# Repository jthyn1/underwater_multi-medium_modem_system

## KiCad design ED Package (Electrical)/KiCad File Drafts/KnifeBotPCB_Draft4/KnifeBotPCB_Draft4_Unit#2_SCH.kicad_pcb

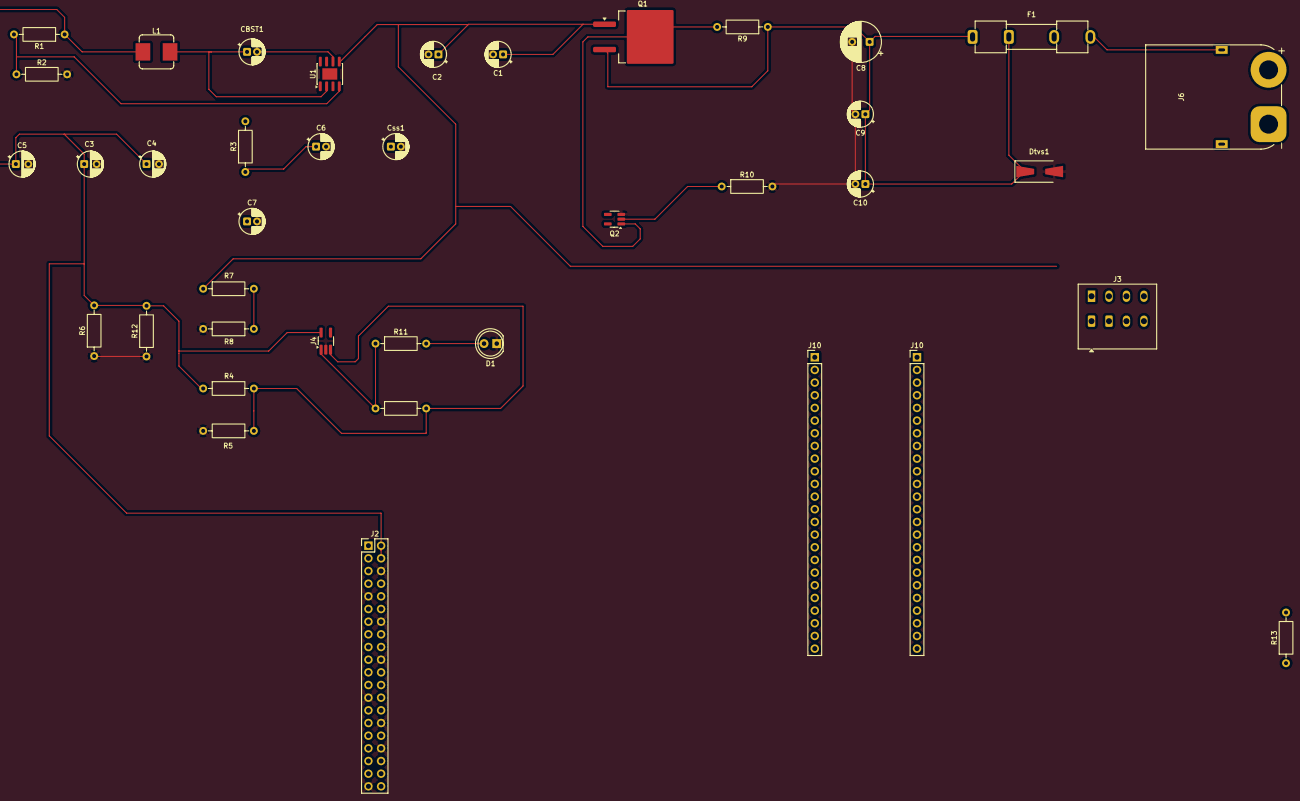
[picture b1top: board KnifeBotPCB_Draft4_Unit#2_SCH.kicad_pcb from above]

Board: 2 copper layers, 39 parts (0 on the bottom side), 17 nets.

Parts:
C1: 10uF; CP_Radial_D5.0mm_P2.00mm
C2, C10: 100nF; CP_Radial_D5.0mm_P2.00mm
C3, C4, C5: 22uF; CP_Radial_D5.0mm_P2.50mm
C6: 33pF; CP_Radial_D5.0mm_P2.00mm
C7: 2.7nF; CP_Radial_D5.0mm_P2.00mm
C8: 100uF; CP_Radial_D8.0mm_P3.50mm
C9: 1uF; CP_Radial_D5.0mm_P2.00mm
CBST1: 100nF; CP_Radial_D5.0mm_P2.00mm
Css1: 10nF; CP_Radial_D5.0mm_P2.00mm
D1: LED; LED_D5.0mm
Dtvs1: SMBJ18A; D_SMA-SMB_Universal_Handsoldering
F1: 5A; Fuseholder_Clip-5x20mm_Keystone_3512_Inline_P23.62x7.27mm_D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
J2: Raspberry_Pi_5; PinHeader_2x20_P2.54mm_Vertical
J3: WAGO 2604-3104PCB terminal block; TerminalBlock_WAGO_2601-3104_1x04_P3.50mm_Vertical
J4: TLV7031; TSOT-23-5_HandSoldering
J6: XT90PW-M; AMASS_XT90PW-M_1x02_P10.90mm_Horizontal
J10, J10#2: Teensy 4.1; PinHeader_1x24_P2.54mm_Vertical
L1: 3.6uH; L_Bourns_SRP7028A_7.3x6.6mm
Q1: F5305S PMOS; TO-263-2
Q2: BSS138 NMOS; SOT-23-5_HandSoldering
R1: 55k; R_Axial_DIN0207_L6.3mm_D2.5mm_P10.16mm_Horizontal
R2, R5, R8: 10k; R_Axial_DIN0207_L6.3mm_D2.5mm_P10.16mm_Horizontal
R3: 15.8k; R_Axial_DIN0207_L6.3mm_D2.5mm_P10.16mm_Horizontal
R4: 25.86k; R_Axial_DIN0207_L6.3mm_D2.5mm_P10.16mm_Horizontal
R6, R9, R10: 100k; R_Axial_DIN0207_L6.3mm_D2.5mm_P10.16mm_Horizontal
R7: 90k; R_Axial_DIN0207_L6.3mm_D2.5mm_P10.16mm_Horizontal
R11: 1k; R_Axial_DIN0207_L6.3mm_D2.5mm_P10.16mm_Horizontal
R12: 500k; R_Axial_DIN0207_L6.3mm_D2.5mm_P10.16mm_Horizontal
R13: 4.7k; R_Axial_DIN0207_L6.3mm_D2.5mm_P10.16mm_Horizontal
Rhys1: 470k; R_Axial_DIN0207_L6.3mm_D2.5mm_P10.16mm_Horizontal
U1: AP64501SP-13; SOIC-8-1EP_3.9x4.9mm_P1.27mm_EP2.29x3mm

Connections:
5V/5A: C3.1, C4.1, C5.1, J2.2 (5V), J2.4 (5V), J4.5 (VCC), L1.1, R1.1, R4.1, R6.2, R12.2
+VBATT: C1.1, C2.1, Q1.1 (D), R7.1, U1.3 (VIN), U1.5 (EN)
/1.45V Low Batt ref: J4.3 (In+), R4.2, R5.1, Rhys1.2
/Sensors&Teensy/Any Digital Pin: J10.23 (AIN1), R13.1
GND: C1.2, C2.2, C3.2, C4.2, C5.2, C6.2, C7.2, C8.2, C9.2, C10.2, Css1.2, D1.1 (K), Dtvs1.2 (A2), J2.6 (GND), J2.9 (GND), J2.14 (GND), J2.20 (GND), J2.25 (GND), J2.30 (GND), J2.34 (GND), J2.39 (GND), J4.2 (VEE), Q2.3 (S), R2.2, R5.2, R6.1, R8.2, R10.2, R12.1, U1.1 (GND)
unnamed: C7.1, R3.2
unnamed: D1.2 (A), R11.2
unnamed: C8.1, C9.1, C10.1, Dtvs1.1 (A1), F1.1, Q1.3 (S), R9.1
unnamed: J4.4 (In-), R7.2, R8.1
unnamed: J4.1 (Out), R11.1, Rhys1.1
unnamed: Q1.2 (G), Q2.1 (D), R9.2
unnamed: C6.1, R3.1, U1.7 (COMP)
unnamed: Css1.1, U1.8 (SS)
unnamed: CBST1.1, L1.2, U1.2 (SW)
unnamed: CBST1.2, U1.6 (VBST)
unnamed: R1.2, R2.1, U1.4 (VFB)
Stay_On: Q2.2 (G), R10.1

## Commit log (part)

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2026-06-15 Create Main Software
2026-06-15 Hardware/Documentation
    All of the hardware design files and documentation for components
2026-06-15 Software
    All of the different software files for the project
